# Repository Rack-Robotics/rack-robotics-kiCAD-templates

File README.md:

# Rack Robotics KICAD Templates
Templates for use by Rack Robotics, Inc. & friends

Design rules for JLCPCB PCBs are generated using the [JLCPCB design rules](https://jlcpcb.com/capabilities/pcb-capabilities). 
Design rules for PCBway PCBs are generated using the [PCBway design rules](https://www.pcbway.com/capabilities.html).

# Templates 
The included templates are: 

**FR4 PCB Templates** 
- RP2040 Microcontroller, 4-layer 1 oz outer 0.5 oz inner FR4 PCB
- 4-layer 1 oz outer 0.5 oz inner FR4 PCB

**Flex PCB Templates**
- 2-layer 1 oz flex PCB 
- 2-layer 0.5 oz flex PCB

**Aluminum PCB Templates**
- 1-layer 1 oz aluminum PCB

# How to Use Templates in KiCAD 

To use these templates in KiCAD: 

- clone repo to local directory of choice 
- open KiCAD 
- select 'file' 
- click 'New Project from Template' 
- click 'User Templates
- select the local repo directory
- select your template of interest

A new KiCAD project will be created using the template you have selected. 

# Contribution 

**Rules for Contribution** 
 - ensure that templates follow up-to-date design rules from the indicated fabrication house (JLCPCB,PCBway, ect)
 - ensure that schematic 'page settings' are consistent with existing templates (issue date, revision convention, title, company)
 - ensure that PCB 'board setup' is consistent and accurate (physical setup, board finish, text & graphics, design rules)
 - name templates according to pcb type, layer count, copper weight, and fabrication house (JLCPCB, PCBway, ect)
 - ensure that info.html is updated for each template with the correct information

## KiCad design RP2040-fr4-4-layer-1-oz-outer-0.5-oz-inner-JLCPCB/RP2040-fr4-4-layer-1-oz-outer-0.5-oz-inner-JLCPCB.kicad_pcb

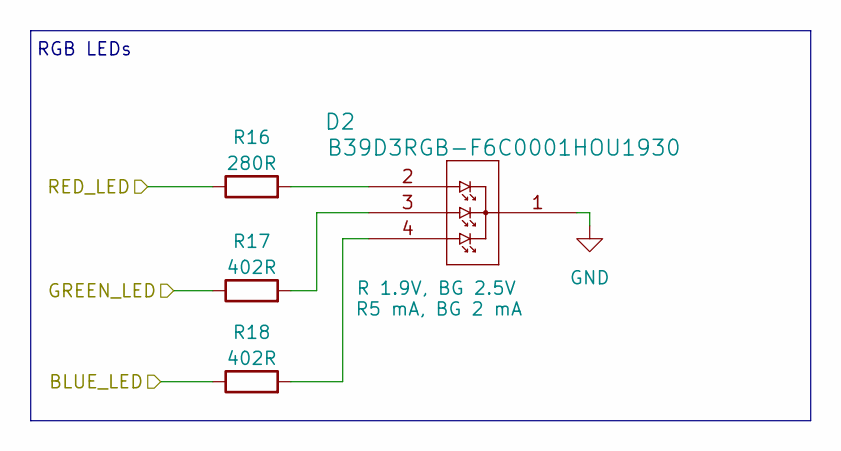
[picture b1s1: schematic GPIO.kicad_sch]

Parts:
D2: B39D3RGB-F6C0001HOU1930
R16: 280R; R_0402_1005Metric; Tolerance 1%
R17, R18: 402R; R_0402_1005Metric; Tolerance 1%

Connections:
/GPIO/BLUE_LED: R18.1; also elsewhere on the board
/GPIO/GREEN_LED: R17.1; also elsewhere on the board
/GPIO/RED_LED: R16.1; also elsewhere on the board
GND: D2.1; also elsewhere on the board
unnamed: D2.2, R16.2
unnamed: D2.3, R17.2
unnamed: D2.4, R18.2

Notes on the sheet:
RGB LEDs

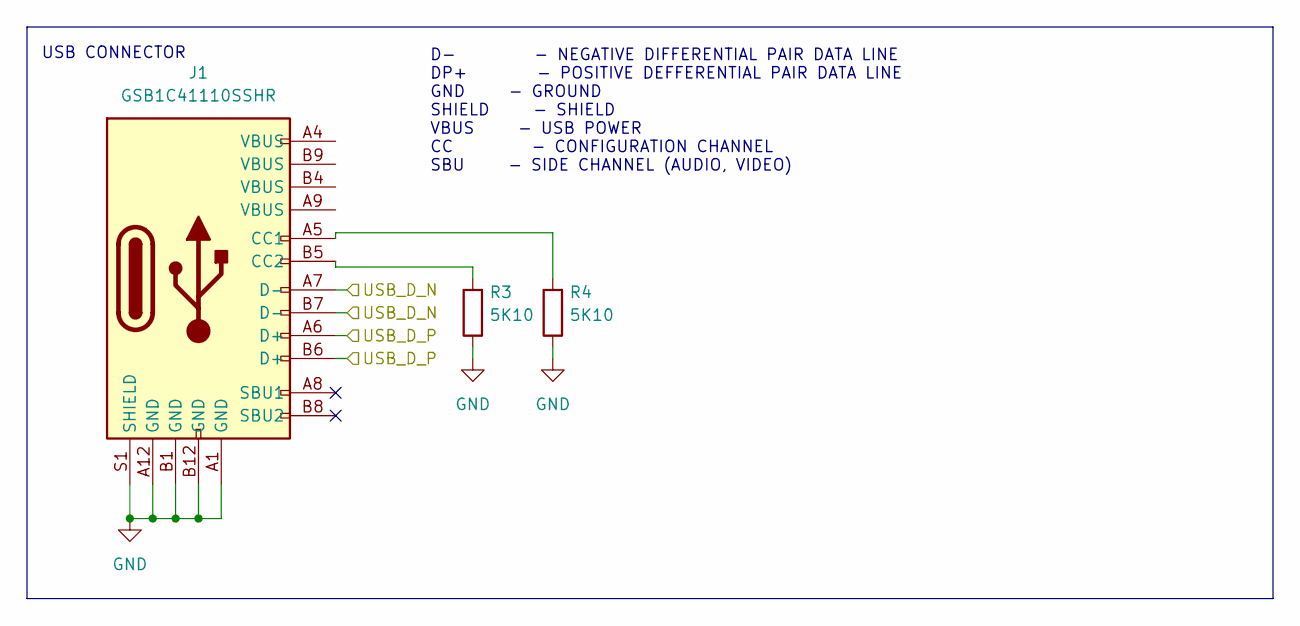
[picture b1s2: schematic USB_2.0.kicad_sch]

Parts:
J1: GSB1C41110SSHR; Part Number GSB1C41110SSHR
R3, R4: 5K10; R_0402_1005Metric; Tolerance 1%

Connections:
/USB_2.0/USB_D_N: J1.A7 (D-), J1.B7 (D-); also elsewhere on the board
/USB_2.0/USB_D_P: J1.A6 (D+), J1.B6 (D+); also elsewhere on the board
GND: J1.A1 (GND), J1.A12 (GND), J1.B1 (GND), J1.B12 (GND), J1.S1 (SHIELD), R3.1, R4.1; also elsewhere on the board
unnamed: J1.A5 (CC1), R4.2
unnamed: J1.B5 (CC2), R3.2

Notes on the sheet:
D- - NEGATIVE DIFFERENTIAL PAIR DATA LINE DP+ - POSITIVE DEFFERENTIAL PAIR DATA LINE GND - GROUND SHIELD - SHIELD VBUS - USB POWER CC - CONFIGURATION CHANNEL SBU - SIDE CHANNEL (AUDIO, VIDEO)
USB CONNECTOR

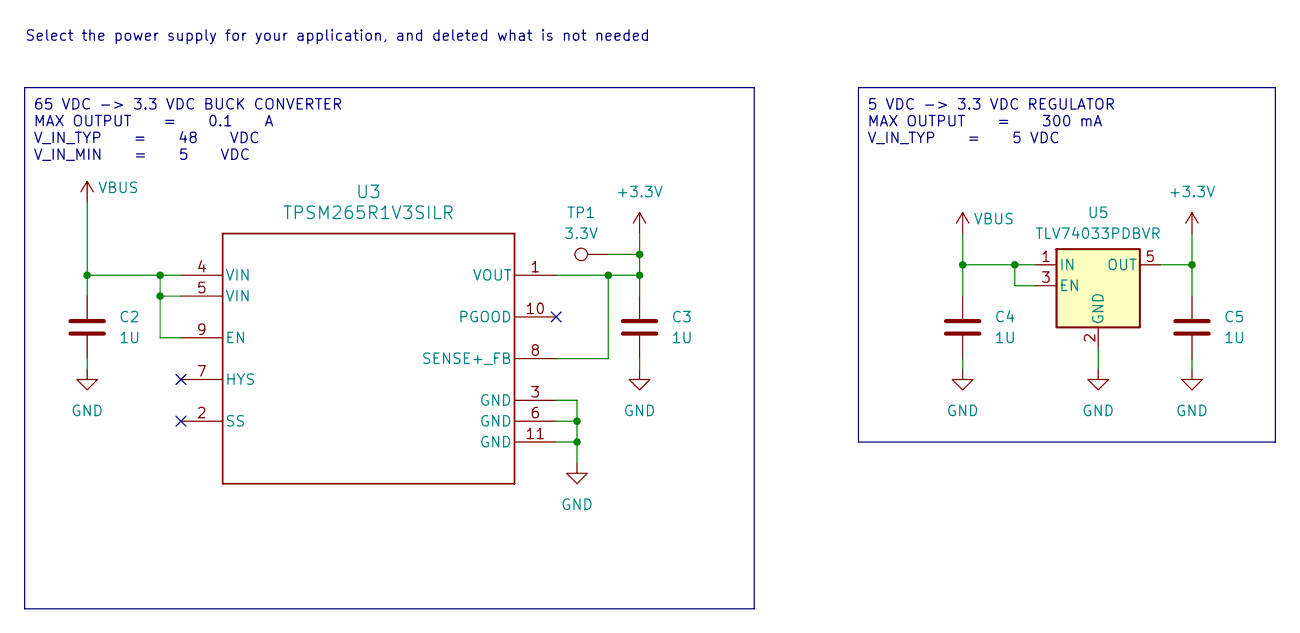
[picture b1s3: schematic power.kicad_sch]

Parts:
C2, C3, C4, C5: 1U; C_0402_1005Metric; Max Voltage 50V; Tolerance 10%
TP1: 3.3V; TestPoint_Pad_1.0x1.0mm
U3: TPSM265R1V3SILR; TPSM265R1
U5: TLV74033PDBVR; SOT-23-5

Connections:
+3.3V: C3.1, C5.1, TP1.1, U3.1 (VOUT), U3.8 (SENSE+_FB), U5.5 (OUT); also elsewhere on the board
GND: C2.2, C3.2, C4.2, C5.2, U3.3 (GND), U3.6 (GND), U3.11 (GND), U5.2 (GND); also elsewhere on the board
VBUS: C2.1, C4.1, U3.4 (VIN), U3.5 (VIN), U3.9 (EN), U5.1 (IN), U5.3 (EN)

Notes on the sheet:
Select the power supply for your application, and deleted what is not needed
5 VDC -> 3.3 VDC REGULATOR MAX OUTPUT = 300 mA V_IN_TYP = 5 VDC
65 VDC -> 3.3 VDC BUCK CONVERTER MAX OUTPUT = 0.1 A V_IN_TYP = 48 VDC V_IN_MIN = 5 VDC

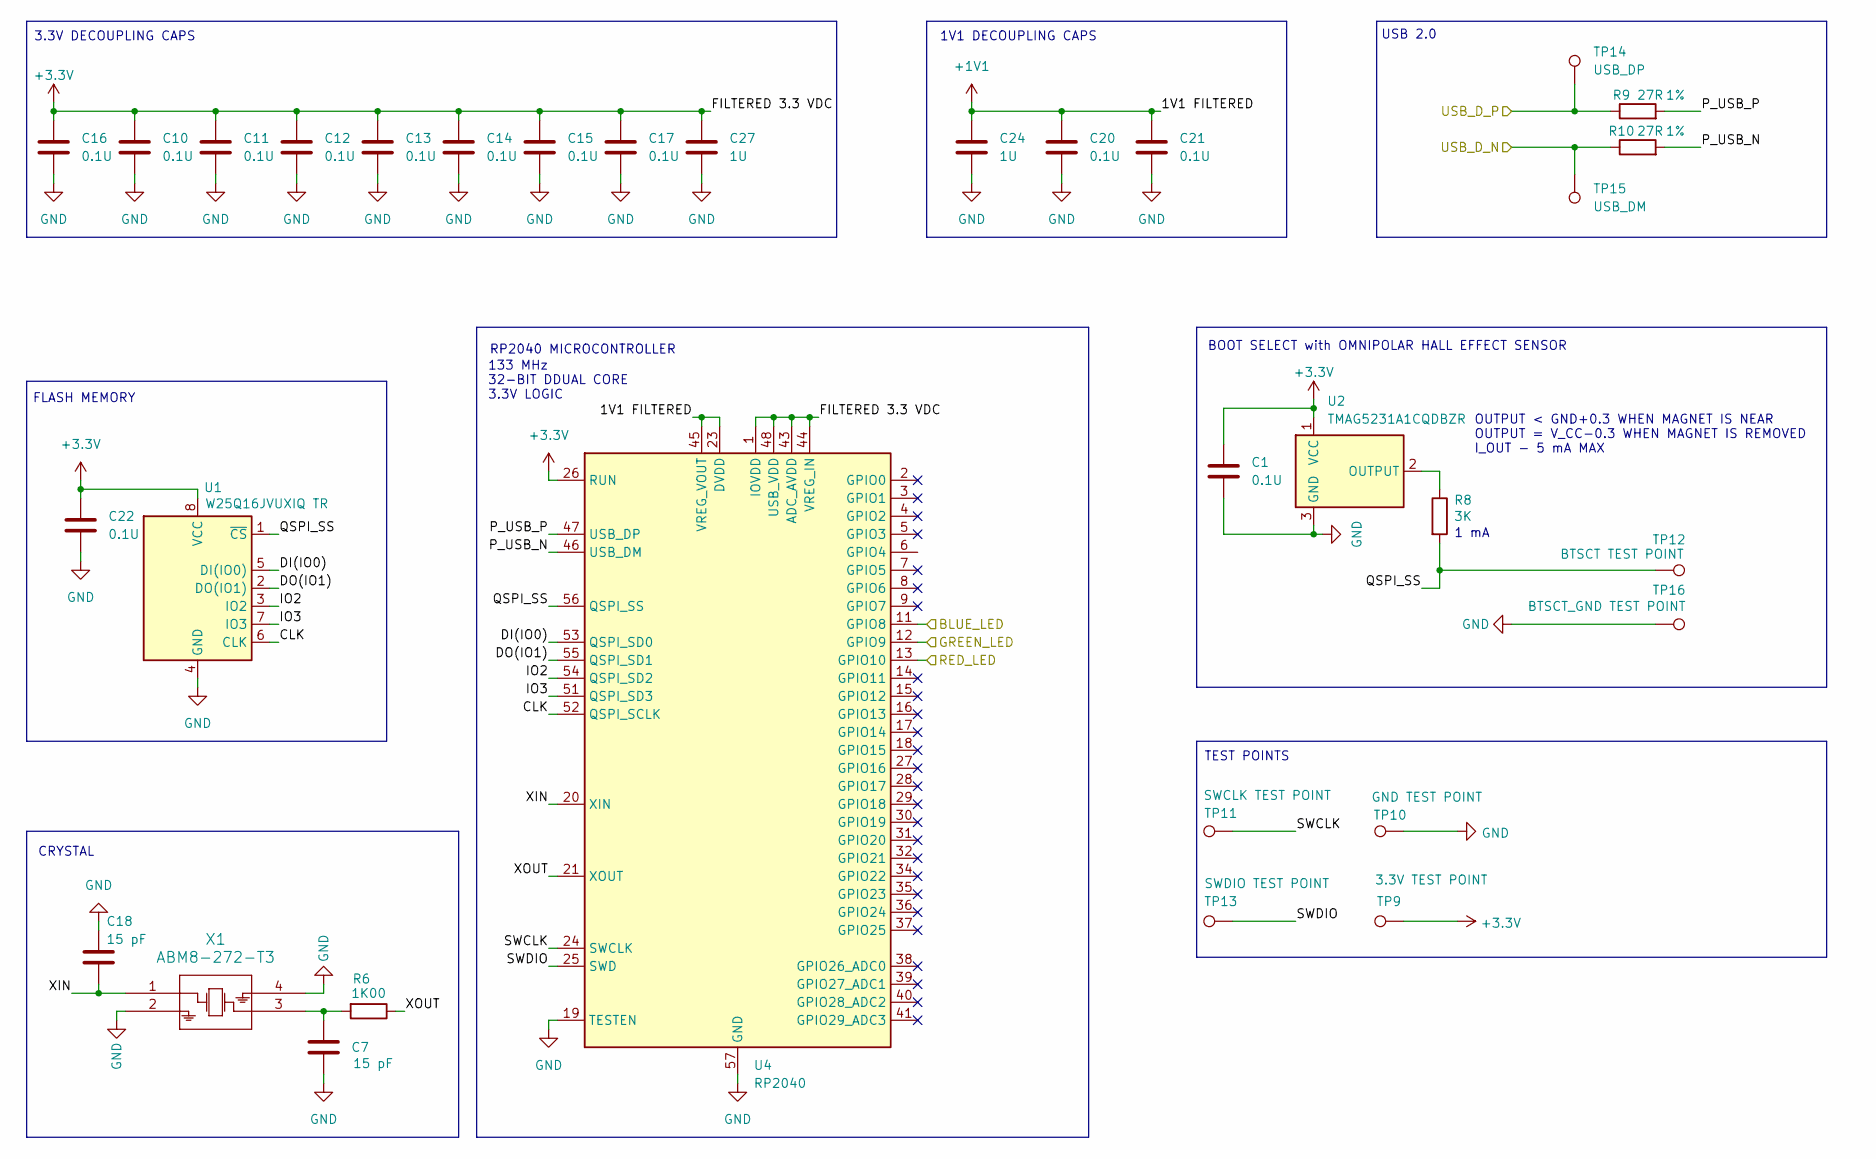
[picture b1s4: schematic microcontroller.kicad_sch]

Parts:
C1, C10, C11, C12, C13, C14, C15, C16, C17, C20, C21, C22: 0.1U; C_0402_1005Metric; Tolerance 10%; Max Voltage 50V
C7, C18: 15 pF; C_0402_1005Metric; Max Voltage 50V; Tolerance 5%
C24, C27: 1U; C_0402_1005Metric; Max Voltage 50V; Tolerance 10%
R6: 1K00; R_0402_1005Metric; Tolerance 1%
R8: 3K; R_0402_1005Metric; Tolerance 1%
R9, R10: 27R; R_0402_1005Metric; Tolerance 1%
TP9: 3.3V TEST POINT; TestPoint_Pad_1.0x1.0mm
TP10: GND TEST POINT; TestPoint_Pad_1.0x1.0mm
TP11: SWCLK TEST POINT; TestPoint_Pad_1.0x1.0mm
TP12: BTSCT TEST POINT; TestPoint_Pad_1.0x1.0mm
TP13: SWDIO TEST POINT; TestPoint_Pad_1.0x1.0mm
TP14: USB_DP; TestPoint_Pad_1.0x1.0mm
TP15: USB_DM; TestPoint_Pad_1.0x1.0mm
TP16: BTSCT_GND TEST POINT; TestPoint_Pad_1.0x1.0mm
U1: W25Q16JVUXIQ TR; W25Q16JVUXIQ_TR
U2: TMAG5231A1CQDBZR; SOT-23
U4: RP2040; QFN-56-1EP_7x7mm_P0.4mm_EP3.2x3.2mm
X1: ABM8-272-T3

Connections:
+1V1: C20.1, C21.1, C24.1, U4.23 (DVDD), U4.45 (VREG_VOUT), U4.50 (DVDD)
+3.3V: C1.1, C10.1, C11.1, C12.1, C13.1, C14.1, C15.1, C16.1, C17.1, C22.1, C27.1, TP9.1, U1.8 (VCC), U2.1 (VCC), U4.1 (IOVDD), U4.10 (IOVDD), U4.22 (IOVDD), U4.26 (RUN), U4.33 (IOVDD), U4.42 (IOVDD), U4.43 (ADC_AVDD), U4.44 (VREG_IN), U4.48 (USB_VDD), U4.49 (IOVDD); also elsewhere on the board
/GPIO/BLUE_LED: U4.11 (GPIO8); also elsewhere on the board
/GPIO/GREEN_LED: U4.12 (GPIO9); also elsewhere on the board
/GPIO/RED_LED: U4.13 (GPIO10); also elsewhere on the board
/USB_2.0/USB_D_N: R9.1, TP14.1; also elsewhere on the board
/USB_2.0/USB_D_P: R10.1, TP15.1; also elsewhere on the board
/microcontroller/CLK: U1.6 (CLK), U4.52 (QSPI_SCLK)
/microcontroller/DI(IO0): U1.5 (DI(IO0)), U4.53 (QSPI_SD0)
/microcontroller/DO(IO1): U1.2 (DO(IO1)), U4.55 (QSPI_SD1)
/microcontroller/IO2: U1.3 (IO2), U4.54 (QSPI_SD2)
/microcontroller/IO3: U1.7 (IO3), U4.51 (QSPI_SD3)
/microcontroller/P_USB_N: R10.2, U4.46 (USB_DM)
/microcontroller/P_USB_P: R9.2, U4.47 (USB_DP)
/microcontroller/QSPI_SS: R8.2, TP12.1, U1.1 (~CS), U4.56 (QSPI_SS)
/microcontroller/SWCLK: TP11.1, U4.24 (SWCLK)
/microcontroller/SWDIO: TP13.1, U4.25 (SWD)
/microcontroller/XIN: C18.2, U4.20 (XIN), X1.1
/microcontroller/XOUT: R6.1, U4.21 (XOUT)
GND: C1.2, C7.2, C10.2, C11.2, C12.2, C13.2, C14.2, C15.2, C16.2, C17.2, C18.1, C20.2, C21.2, C22.2, C24.2, C27.2, TP10.1, TP16.1, U1.4 (GND), U2.3 (GND), U4.19 (TESTEN), U4.57 (GND), X1.2, X1.4; also elsewhere on the board
unnamed: C7.1, R6.2, X1.3
unnamed: R8.1, U2.2 (OUTPUT)

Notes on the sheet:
RP2040 MICROCONTROLLER
133 MHz 32-BIT DDUAL CORE 3.3V LOGIC
OUTPUT < GND+0.3 WHEN MAGNET IS NEAR OUTPUT = V_CC-0.3 WHEN MAGNET IS REMOVED I_OUT - 5 mA MAX
TEST POINTS
BOOT SELECT with OMNIPOLAR HALL EFFECT SENSOR
1V1 DECOUPLING CAPS
USB 2.0
CRYSTAL
FLASH MEMORY
3.3V DECOUPLING CAPS
1 mA

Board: 4 copper layers, 46 parts (0 on the bottom side), 28 nets, no tracks yet.

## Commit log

2024-08-07 added flex PCB templates
    added templates for JLCPCB 2-layer flex PCBs with 1 oz and 0.5 oz copper
2024-08-07 updated info.html and readme
2024-08-07 added aluminum PCB from JLCPCB
2024-08-08 added 4-layer FR4 PCB
2024-08-08 added RP2040 PCB template
2024-08-08 updated USB terminology
2024-08-18 added USB & power
2024-08-20 updated fr4-pcb-4-layers to new JLCPCB design rules
